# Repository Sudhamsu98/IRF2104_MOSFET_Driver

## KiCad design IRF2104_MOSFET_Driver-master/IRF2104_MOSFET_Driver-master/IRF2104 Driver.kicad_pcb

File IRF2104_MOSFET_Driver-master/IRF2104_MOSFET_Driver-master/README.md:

# IRF2104_MOSFET_Driver
IRF2104 based MOSFET Driver

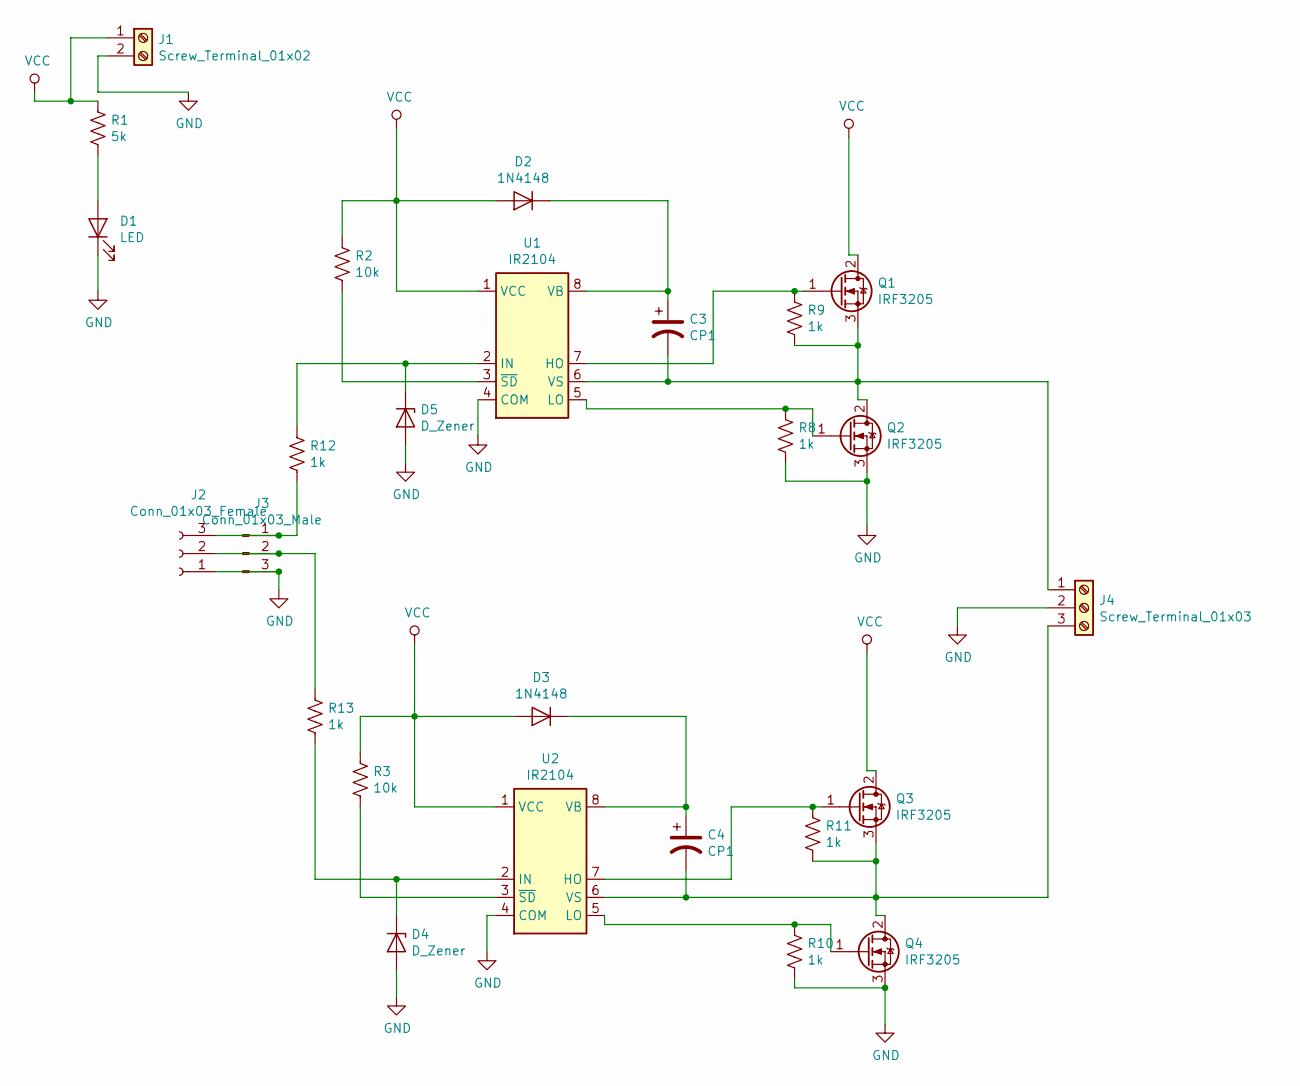
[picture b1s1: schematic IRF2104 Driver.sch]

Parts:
C3, C4: CP1; C_Axial_L3.8mm_D2.6mm_P7.50mm_Horizontal
D1: LED; LED_D5.0mm
D2, D3: 1N4148; D_DO-35_SOD27_P7.62mm_Horizontal
D4, D5: D_Zener; D_DO-35_SOD27_P7.62mm_Horizontal
J1: Screw_Terminal_01x02; TerminalBlock_bornier-2_P5.08mm
J2: Conn_01x03_Female; PinHeader_1x03_P2.54mm_Vertical
J3: Conn_01x03_Male; PinHeader_1x03_P2.54mm_Vertical
J4: Screw_Terminal_01x03; TerminalBlock_bornier-3_P5.08mm
Q1, Q2, Q3, Q4: IRF3205; TO-220-3_Vertical
R1: 5k; R_Axial_DIN0207_L6.3mm_D2.5mm_P7.62mm_Horizontal
R2, R3: 10k; R_Axial_DIN0207_L6.3mm_D2.5mm_P7.62mm_Horizontal
R8, R9, R10, R11, R12, R13: 1k; R_Axial_DIN0207_L6.3mm_D2.5mm_P7.62mm_Horizontal
U1, U2: IR2104; DIP-8_W7.62mm_Socket

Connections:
GND: D1.1 (K), D4.2 (A), D5.2 (A), J1.2, J2.1, J3.3, J4.2, Q2.3 (S), Q4.3 (S), R8.2, R10.2, U1.4 (COM), U2.4 (COM)
unnamed: C3.1, D2.1 (K), U1.8 (VB)
unnamed: C3.2, J4.1, Q1.3 (S), Q2.2 (D), R9.2, U1.6 (VS)
unnamed: C4.1, D3.1 (K), U2.8 (VB)
unnamed: C4.2, J4.3, Q3.3 (S), Q4.2 (D), R11.2, U2.6 (VS)
unnamed: D1.2 (A), R1.2
unnamed: D4.1 (K), R13.2, U2.2 (IN)
unnamed: D5.1 (K), R12.1, U1.2 (IN)
unnamed: J2.2, J3.2, R13.1
unnamed: J2.3, J3.1, R12.2
unnamed: Q1.1 (G), R9.1, U1.7 (HO)
unnamed: Q2.1 (G), R8.1, U1.5 (LO)
unnamed: Q3.1 (G), R11.1, U2.7 (HO)
unnamed: Q4.1 (G), R10.1, U2.5 (LO)
unnamed: R2.2, U1.3 (~SD)
unnamed: R3.2, U2.3 (~SD)
VCC: D2.2 (A), D3.2 (A), J1.1, Q1.2 (D), Q3.2 (D), R1.1, R2.1, R3.1, U1.1 (VCC), U2.1 (VCC)

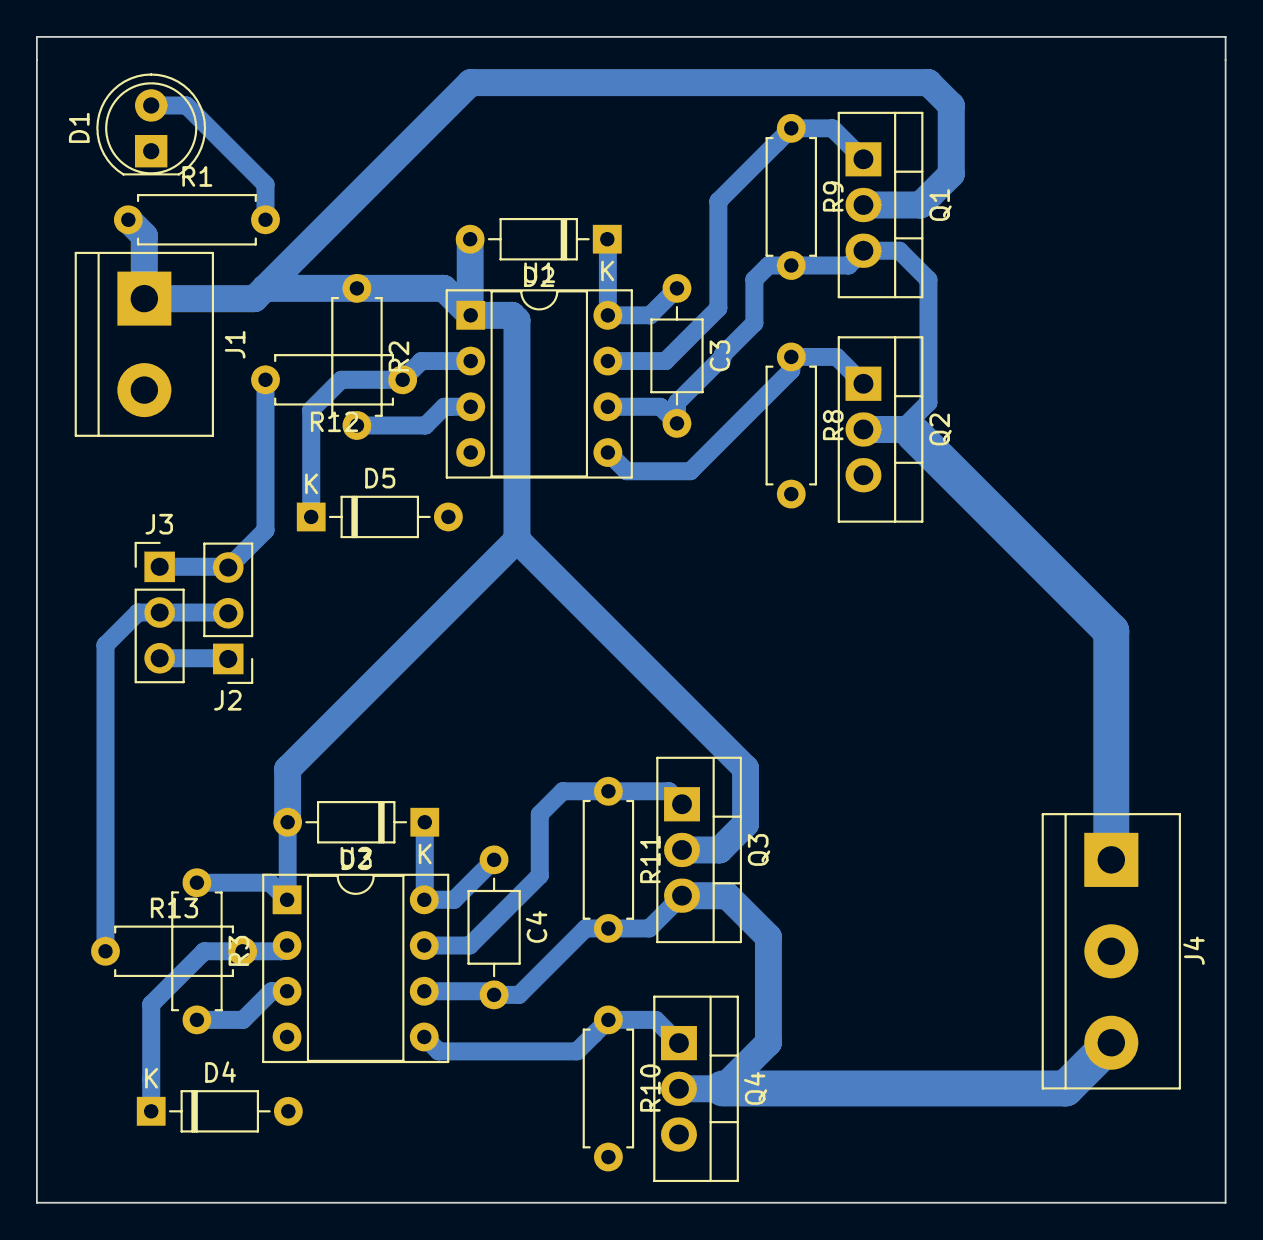
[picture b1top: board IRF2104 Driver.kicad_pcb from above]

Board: 2 copper layers, 66.0 x 64.8 mm, 26 parts (0 on the bottom side), 17 nets.

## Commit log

2019-08-23 initia com
2019-10-06 Revised PCB
    i have made changes to the PCB of the mosfet driver originally created by Davadatta.
